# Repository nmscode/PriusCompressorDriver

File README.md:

# Prius Compressor Driver
 
This is a driver that is meant to work with SIMPLEFOC to drive a Prius Compressor Motor at 200V from 120V mains.

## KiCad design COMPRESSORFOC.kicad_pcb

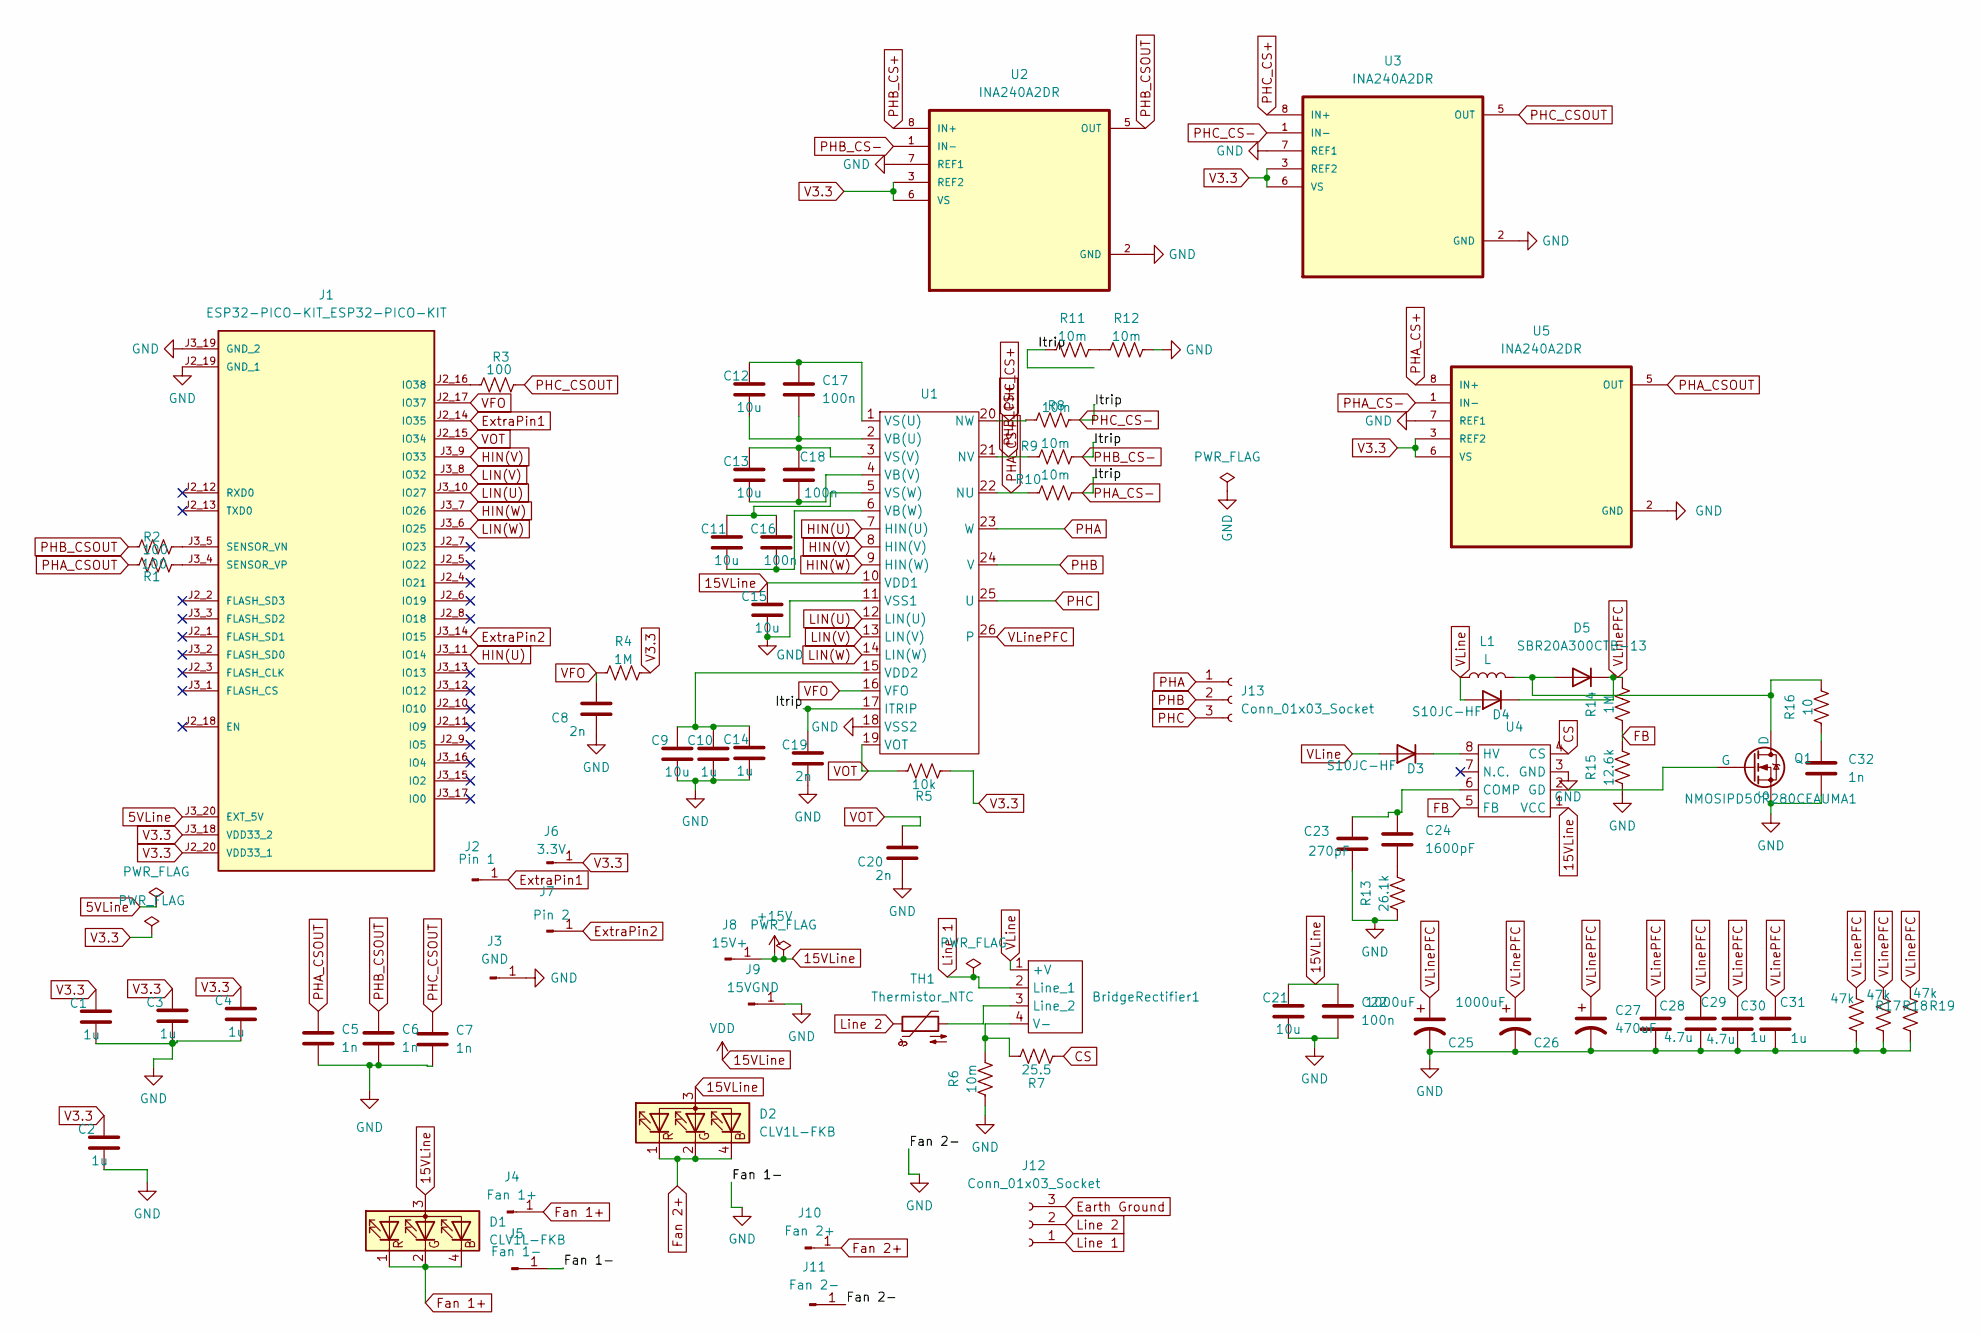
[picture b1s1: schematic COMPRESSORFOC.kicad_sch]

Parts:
BridgeRectifier1: KBJ-2 Rectifier
C1, C2, C3, C4, C10, C14: 1u; C_0603_1608Metric_Pad1.08x0.95mm_HandSolder
C5, C6, C7: 1n; C_0603_1608Metric_Pad1.08x0.95mm_HandSolder
C8, C19, C20: 2n; C_0603_1608Metric_Pad1.08x0.95mm_HandSolder
C9, C11, C12, C13, C15, C21: 10u; C_0805_2012Metric_Pad1.18x1.45mm_HandSolder
C16, C17, C18, C22: 100n; C_0603_1608Metric_Pad1.08x0.95mm_HandSolder
C23: 270pF; C_0603_1608Metric_Pad1.08x0.95mm_HandSolder
C24: 1600pF; C_0603_1608Metric_Pad1.08x0.95mm_HandSolder
C25, C26: 1000uF; 1000uCap
C27: 470uF; 470uFCap
C28, C29: 4.7u; 4.7uCap
C30, C31: 1u; C_2225_5664Metric_Pad1.80x6.60mm_HandSolder
C32: 1n; snubber_capacitor
D1, D2: CLV1L-FKB; LED_Cree-PLCC4_3.2x2.8mm_CCW
D3, D4: S10JC-HF; D_SMC_Handsoldering
D5: SBR20A300CTB-13; TO-263-2-FOC
J1: ESP32-PICO-KIT_ESP32-PICO-KIT; XCVR_ESP32-PICO-KIT; PARTREV 4.1
J2: Pin 1; SolderWire-1.5sqmm_1x01_D1.7mm_OD3.9mm
J3: GND; SolderWire-1.5sqmm_1x01_D1.7mm_OD3.9mm
J4: Fan 1+; SolderWire-1.5sqmm_1x01_D1.7mm_OD3.9mm
J5: Fan 1-; SolderWire-1.5sqmm_1x01_D1.7mm_OD3.9mm
J6: 3.3V; SolderWire-1.5sqmm_1x01_D1.7mm_OD3.9mm
J7: Pin 2; SolderWire-1.5sqmm_1x01_D1.7mm_OD3.9mm
J8: 15V+; SolderWire-1.5sqmm_1x01_D1.7mm_OD3.9mm
J9: 15VGND; SolderWire-1.5sqmm_1x01_D1.7mm_OD3.9mm
J10: Fan 2+; SolderWire-1.5sqmm_1x01_D1.7mm_OD3.9mm
J11: Fan 2-; SolderWire-1.5sqmm_1x01_D1.7mm_OD3.9mm
J12: Conn_01x03_Socket; IEC_plugin
J13: Conn_01x03_Socket; TerminalBlock3pin
L1: L; WETORINDUCTOR
Q1: NMOSIPD50R280CEAUMA1; TO-252-2
R1, R2, R3: 100; R_0603_1608Metric_Pad0.98x0.95mm_HandSolder
R4, R14: 1M; R_0805_2012Metric_Pad1.20x1.40mm_HandSolder
R5: 10k; R_0603_1608Metric_Pad0.98x0.95mm_HandSolder
R6, R8, R9, R10, R11, R12: 10m; R_2512_6332Metric_Pad1.40x3.35mm_HandSolder
R7: 25.5; R_0603_1608Metric_Pad0.98x0.95mm_HandSolder
R13: 26.1k; R_0603_1608Metric_Pad0.98x0.95mm_HandSolder
R15: 12.6k; R_0603_1608Metric_Pad0.98x0.95mm_HandSolder
R16: 10; snubber_resistor
R17, R18, R19: 47k; R_2512_6332Metric_Pad1.40x3.35mm_HandSolder
TH1: Thermistor_NTC; NTC_compressorfoc
U1: IM323L6G2XKMA1
U2, U3, U5: INA240A2DR; INA240A1DR
U4: SOIC-8_3.9x4.9mm_P1.27mm

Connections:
5VLine: J1.J3_20 (EXT_5V)
15VLine: C15.1, C21.1, C22.1, D1.3 (A), D2.3 (A), J8.1, U1.10 (VDD1), U4.1 (VCC)
CS: R7.1, U4.4 (CS)
Earth Ground: J12.3
ExtraPin1: J1.J2_14 (IO35), J2.1
ExtraPin2: J1.J3_14 (IO15), J7.1
FB: R14.1, R15.2, U4.5 (FB)
Fan 1+: D1.1 (RK), D1.2 (GK), D1.4 (BK), J4.1
Fan 2+: D2.1 (RK), D2.2 (GK), D2.4 (BK), J10.1
GND: C1.2, C2.2, C3.2, C4.2, C5.2, C6.2, C7.2, C8.2, C9.2, C10.2, C14.2, C15.2, C19.2, C20.2, C21.2, C22.2, C23.2, C25.2, C26.2, C27.2, C28.2, C29.2, C30.2, C31.2, C32.2, J1.J2_19 (GND_1), J1.J3_19 (GND_2), J3.1, J5.1, J9.1, J11.1, Q1.3 (S), R6.1, R12.2, R13.1, R15.1, R17.2, R18.2, R19.2, U1.11 (VSS1), U1.18 (VSS2), U2.2 (GND), U2.7 (REF1), U3.2 (GND), U3.7 (REF1), U4.3 (GND), U5.2 (GND), U5.7 (REF1)
HIN(U): J1.J3_11 (IO14), U1.7 (HIN(U))
HIN(V): J1.J3_9 (IO33), U1.8 (HIN(V))
HIN(W): J1.J3_7 (IO26), U1.9 (HIN(W))
LIN(U): J1.J3_10 (IO27), U1.12 (LIN(U))
LIN(V): J1.J3_8 (IO32), U1.13 (LIN(V))
LIN(W): J1.J3_6 (IO25), U1.14 (LIN(W))
Line 1: BridgeRectifier1.2 (Line_1), J12.1
Line 2: J12.2, TH1.1
unnamed: BridgeRectifier1.3 (Line_2), TH1.2
unnamed: BridgeRectifier1.4 (V-), R6.2, R7.2
unnamed: C24.2, R13.2
unnamed: C32.1, R16.1
unnamed: D3.1 (K), U4.8 (HV)
unnamed: D5.1 (A), L1.2, Q1.2 (D), R16.2
unnamed: J1.J2_16 (IO38), R3.1
unnamed: J1.J3_5 (SENSOR_VN), R1.1
unnamed: J1.J3_4 (SENSOR_VP), R2.1
unnamed: Q1.1 (G), U4.2 (GD)
unnamed: R11.2, R12.1
unnamed: C12.2, C17.2, U1.2 (VB(U))
unnamed: C13.2, C18.2, U1.4 (VB(V))
unnamed: C11.2, C16.2, U1.6 (VB(W))
unnamed: C9.1, C10.1, C14.1, U1.15 (VDD2)
unnamed: C12.1, C17.1, U1.1 (VS(U))
unnamed: C13.1, C18.1, U1.3 (VS(V))
unnamed: C11.1, C16.1, U1.5 (VS(W))
unnamed: C23.1, C24.1, U4.6 (COMP)
PHA: J13.1, U1.23 (W)
PHA_CS+: R10.1, U1.22 (NU), U5.8 (IN+)
PHA_CS-: C19.1, R8.2, R9.2, R10.2, R11.1, U1.17 (ITRIP), U2.1 (IN-), U3.1 (IN-), U5.1 (IN-)
PHA_CSOUT: C5.1, R2.2, U5.5 (OUT)
PHB: J13.2, U1.24 (V)
PHB_CS+: R9.1, U1.21 (NV), U2.8 (IN+)
PHB_CSOUT: C6.1, R1.2, U2.5 (OUT)
PHC: J13.3, U1.25 (U)
PHC_CS+: R8.1, U1.20 (NW), U3.8 (IN+)
PHC_CSOUT: C7.1, R3.2, U3.5 (OUT)
V3.3: C1.1, C2.1, C3.1, C4.1, J1.J2_20 (VDD33_1), J1.J3_18 (VDD33_2), J6.1, R4.2, R5.1, U2.3 (REF2), U2.6 (VS), U3.3 (REF2), U3.6 (VS), U5.3 (REF2), U5.6 (VS)
VFO: C8.1, J1.J2_17 (IO37), R4.1, U1.16 (VFO)
VLine: BridgeRectifier1.1 (+V), D3.2 (A), D4.2 (A), L1.1
VLinePFC: C25.1, C26.1, C27.1, C28.1, C29.1, C30.1, C31.1, D4.1 (K), D5.2 (K), R14.2, R17.1, R18.1, R19.1, U1.26
VOT: C20.1, J1.J2_15 (IO34), R5.2, U1.19 (VOT)

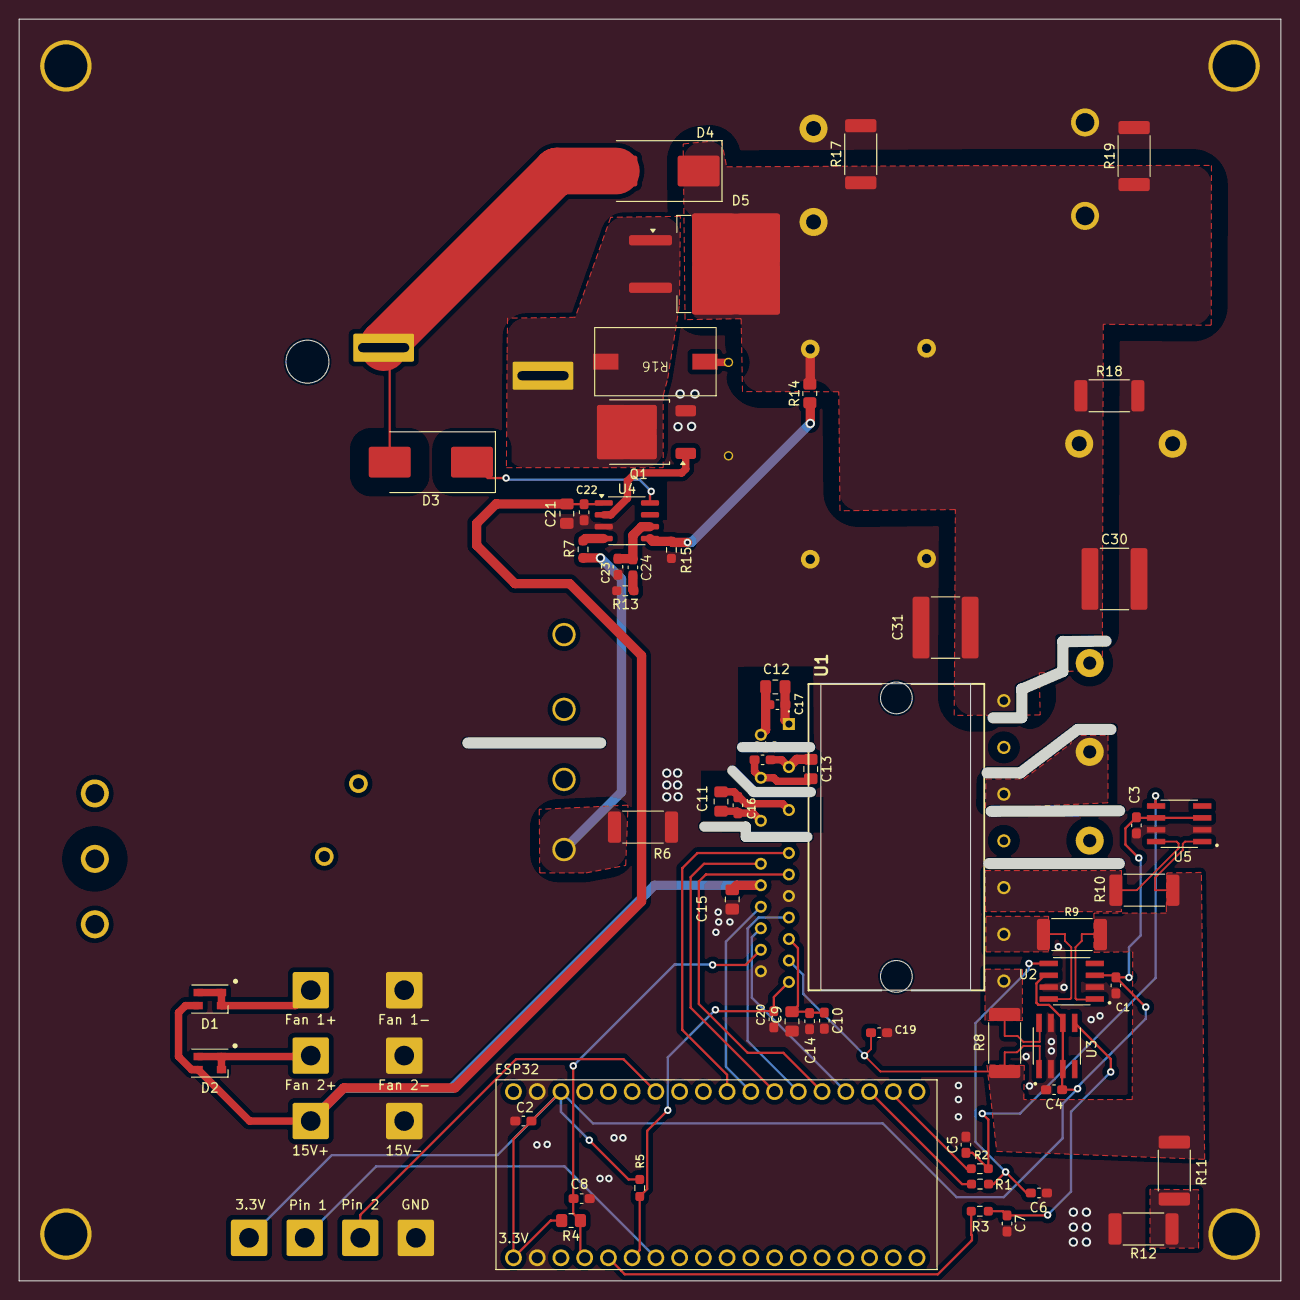
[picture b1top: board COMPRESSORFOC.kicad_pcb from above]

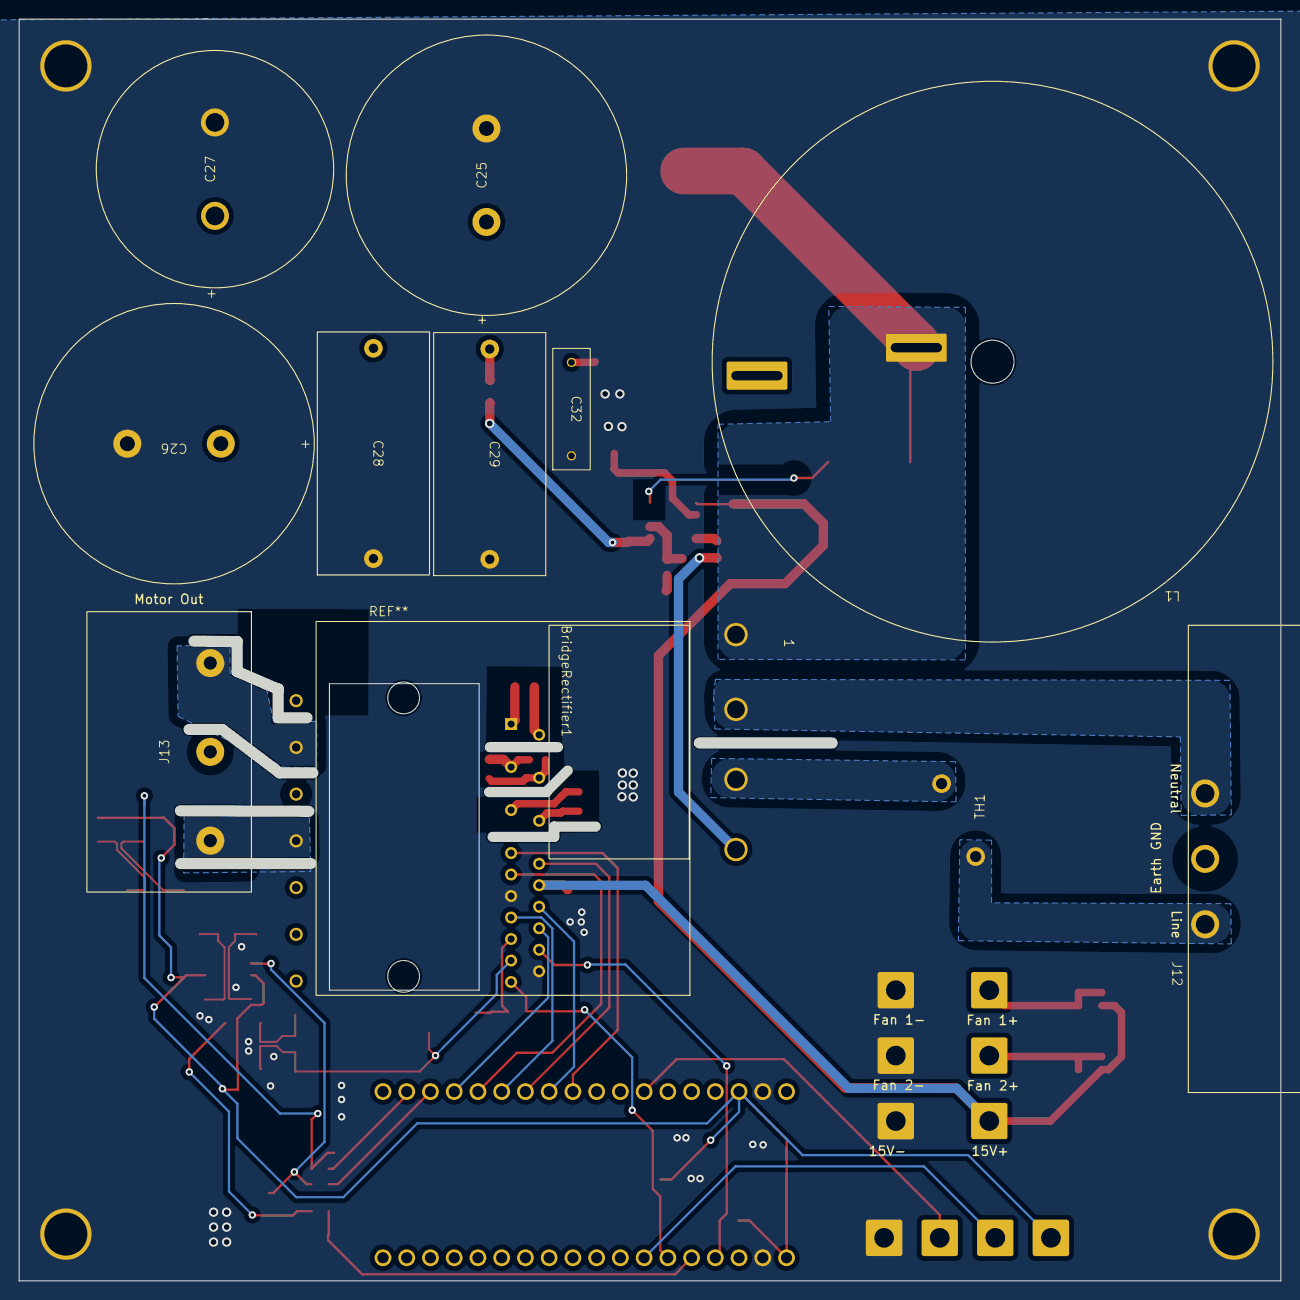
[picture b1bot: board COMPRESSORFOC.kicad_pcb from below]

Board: 2 copper layers, 133.9 x 133.9 mm, 78 parts (10 on the bottom side), 50 nets.

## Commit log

2024-03-01 try jlc assembly workflow
2024-03-01 fix jlc workflow
2024-03-01 workflow typo fix and some erc fixes
2024-03-01 ignore some erc checks
2024-03-01 run for just pushes to main for now
2024-03-01 do not verify for documentation for now
2024-03-01 Add design file PDFs to repo [skip ci]
2024-03-01 Update .gitignore
    [skip ci]
2024-03-01 Update README.md
    [skip ci]
2024-07-14 revised driver
